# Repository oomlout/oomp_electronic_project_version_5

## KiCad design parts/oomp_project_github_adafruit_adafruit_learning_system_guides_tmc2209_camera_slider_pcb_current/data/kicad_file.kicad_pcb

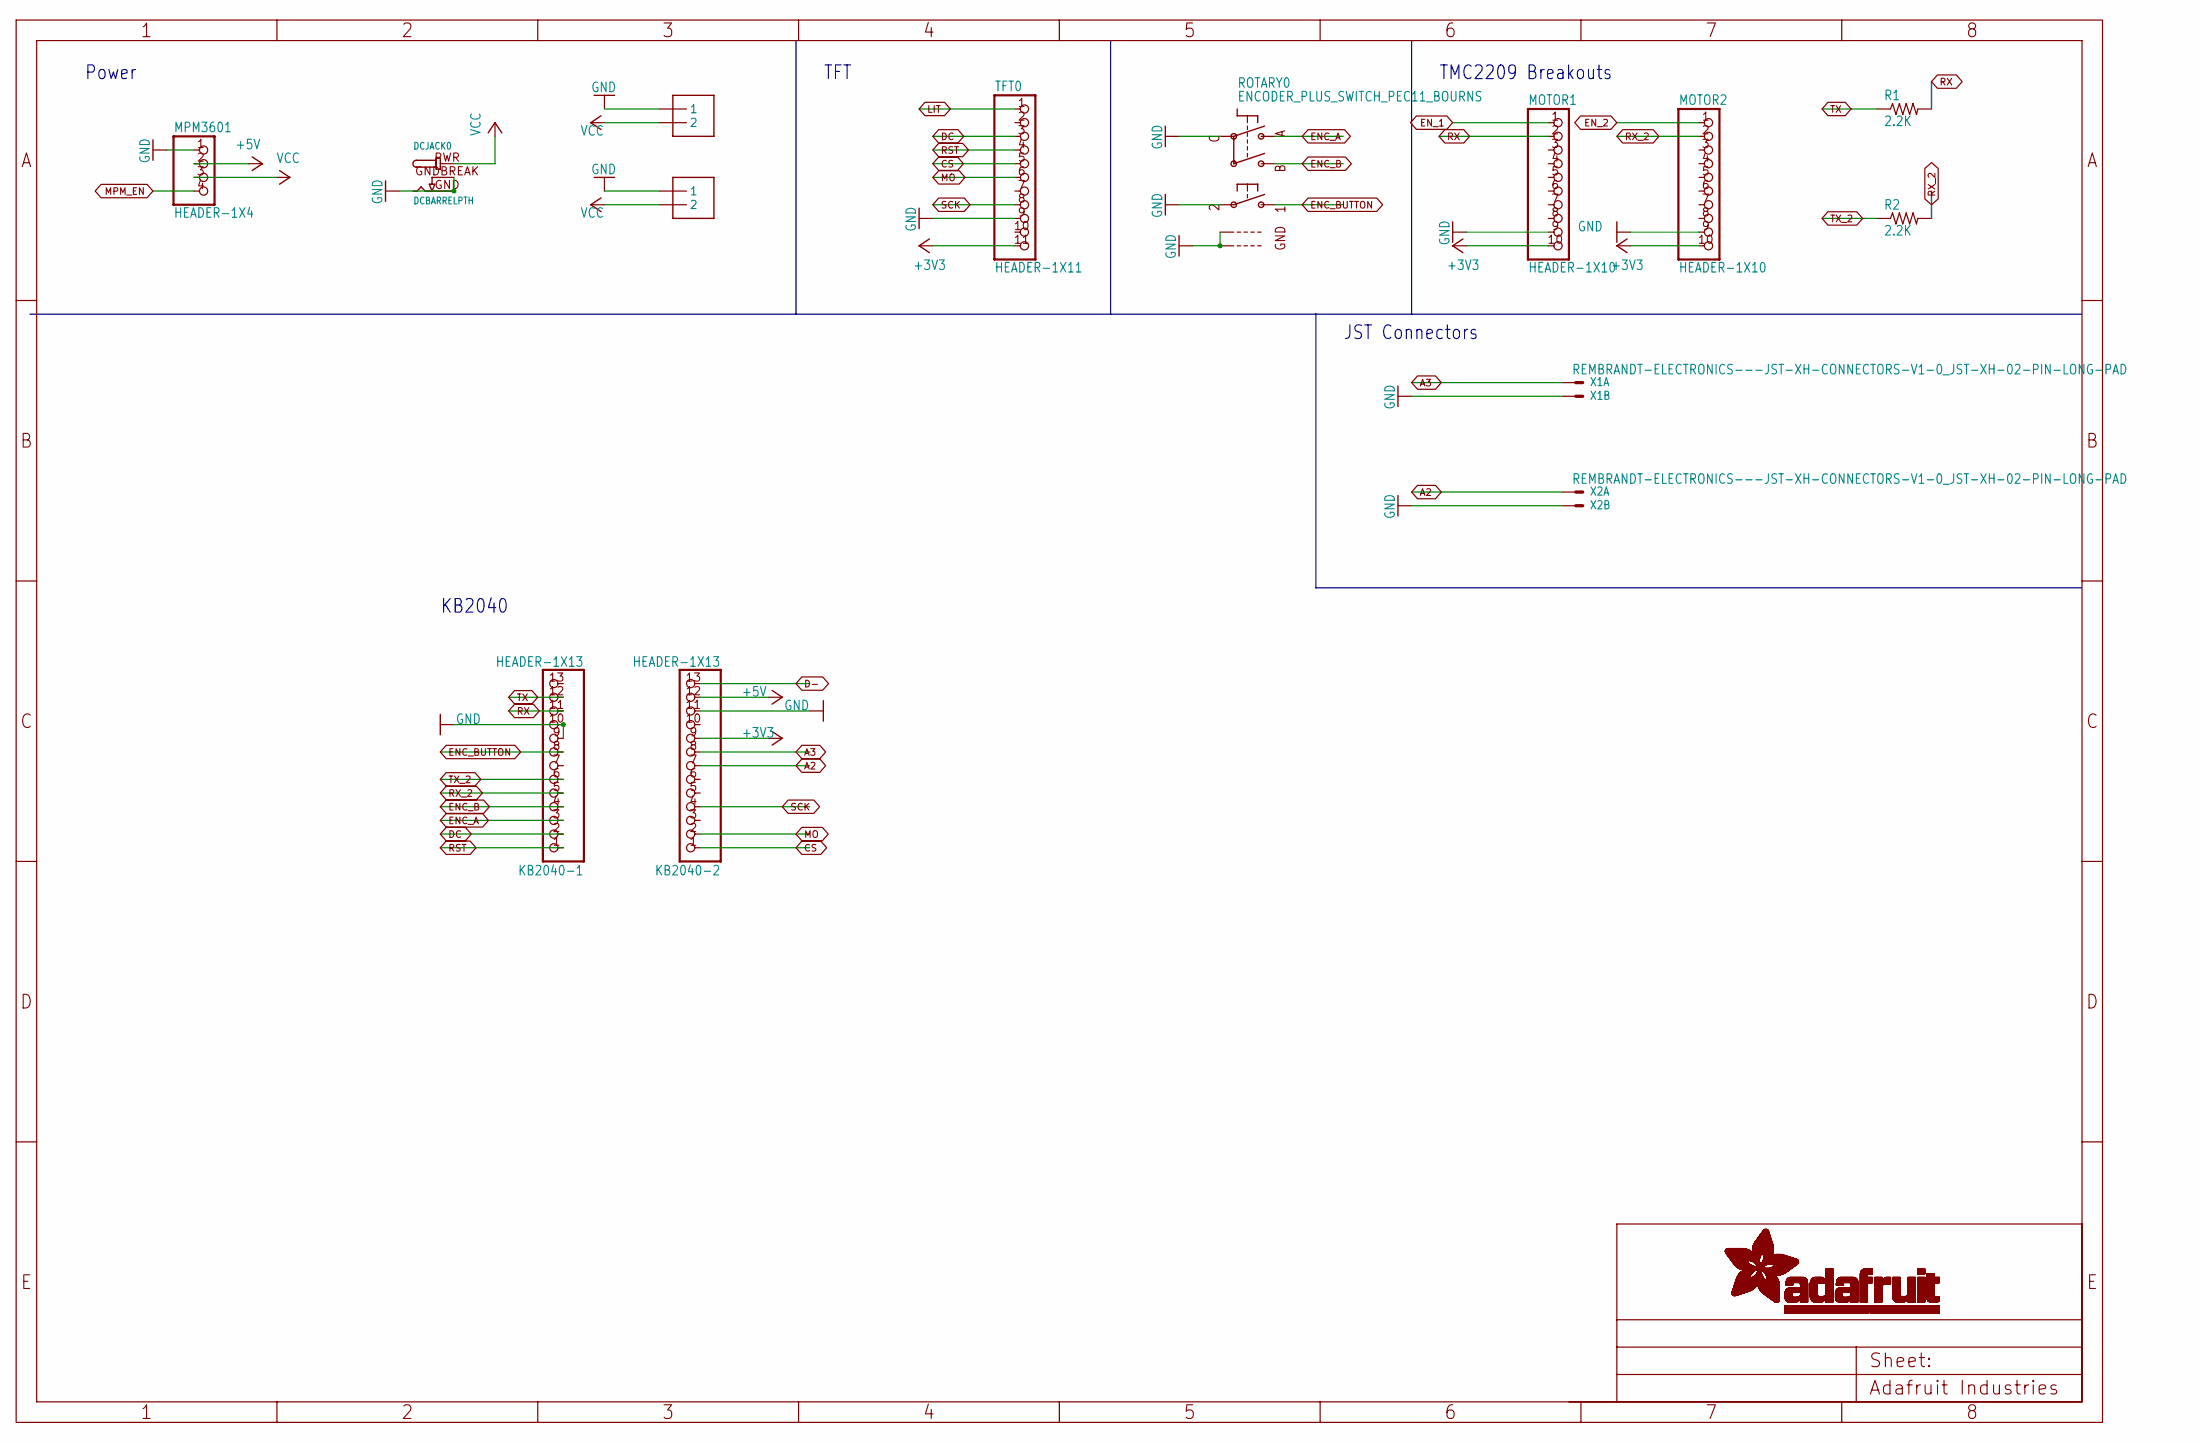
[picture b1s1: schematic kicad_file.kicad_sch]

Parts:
DCJACK0: DCBARRELPTH; DCJACK_2MM_PTH
J1, J2: 1X2-3.5MM
KB2040-1, KB2040-2: HEADER-1X13; 1X13_ROUND_70
MOTOR1, MOTOR2: HEADER-1X10; 1X10_OVAL
MPM3601: HEADER-1X4; 1X04_OVAL
R1, R2: 2.2K; 0309_12
ROTARY0: ENCODER_PLUS_SWITCH_PEC11_BOURNS; PEC11+SWITCH
TFT0: HEADER-1X11; 1X11_ROUND
X1, X2: REMBRANDT-ELECTRONICS---JST-XH-CONNECTORS-V1-0_JS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; REMBRANDT-ELECTRONICS---JST-XH-CONNECTORS-V1-0_JST-XH-02-PA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

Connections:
+3V3: KB2040-2.9, MOTOR1.10, MOTOR2.10, TFT0.11
+5V: KB2040-2.12, MPM3601.2
A2: KB2040-2.7, X2.1
A3: KB2040-2.8, X1.1
CS: KB2040-2.1, TFT0.5
D-: KB2040-2.13
DC: KB2040-1.2, TFT0.3
ENC_A: KB2040-1.3, ROTARY0.P$A
ENC_B: KB2040-1.4, ROTARY0.P$B
ENC_BUTTON: KB2040-1.8, ROTARY0.P$1
EN_1: MOTOR1.1
EN_2: MOTOR2.1
GND: DCJACK0.GND, DCJACK0.GNDBREAK, J1.1, J2.1, KB2040-1.9, KB2040-1.10, KB2040-2.11, MOTOR1.9, MOTOR2.9, MPM3601.1, ROTARY0.P$2, ROTARY0.P$C, ROTARY0.P$GND1, ROTARY0.P$GND2, TFT0.9, X1.2, X2.2
LIT: TFT0.1
MO: KB2040-2.2, TFT0.6
MPM_EN: MPM3601.4
RST: KB2040-1.1, TFT0.4
RX: KB2040-1.11, MOTOR1.2, R1.2
RX_2: KB2040-1.5, MOTOR2.2, R2.2
SCK: KB2040-2.4, TFT0.8
TX: KB2040-1.12, R1.1
TX_2: KB2040-1.6, R2.1
VCC: DCJACK0.PWR, J1.2, J2.2, MPM3601.3

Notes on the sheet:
TFT
JST Connectors
KB2040
TMC2209 Breakouts
Power

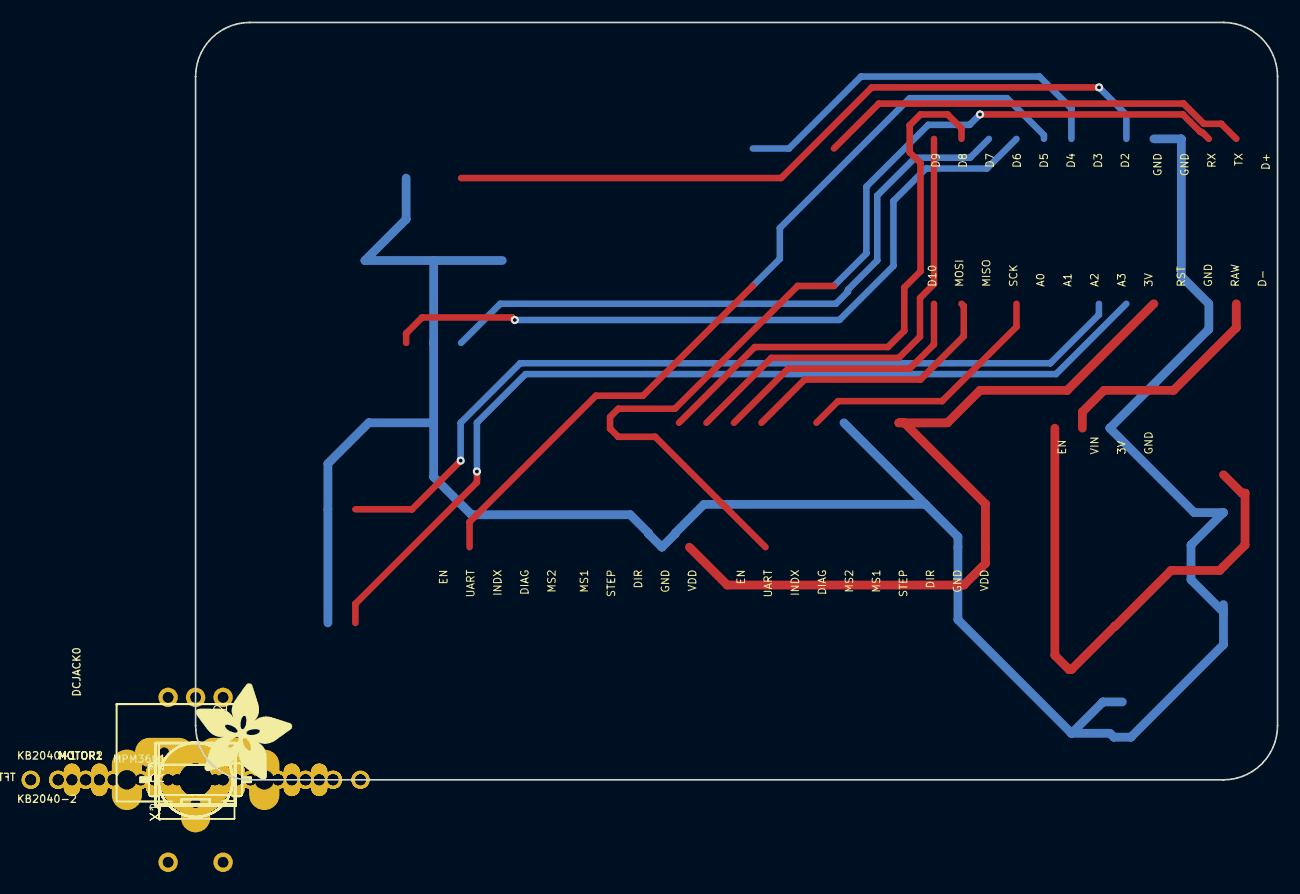
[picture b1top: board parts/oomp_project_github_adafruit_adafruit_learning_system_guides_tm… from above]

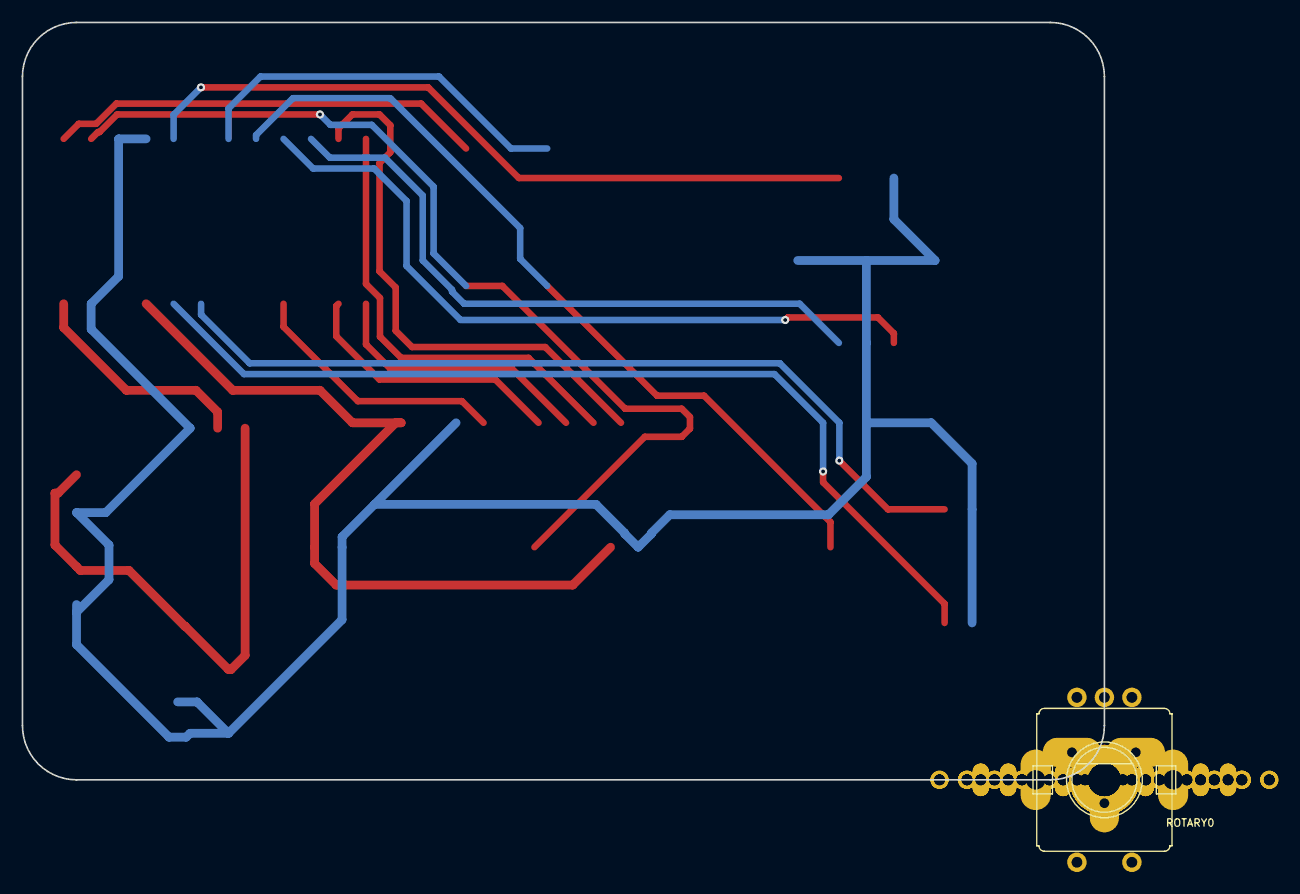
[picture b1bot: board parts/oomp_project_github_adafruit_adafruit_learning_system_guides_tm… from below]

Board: 2 copper layers, 100.0 x 70.0 mm, 114 parts (51 on the bottom side), 18 nets.

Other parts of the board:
E$1, E$2, E$3, E$5: MOUNTINGHOLE_3.0_PLATED
PLABEL0, PLABEL94: PLABEL0
PLABEL1, PLABEL6: PLABEL6
PLABEL2: PLABEL2
PLABEL3: PLABEL3
PLABEL4: PLABEL4
PLABEL5: PLABEL5
PLABEL7, PLABEL95: PLABEL1
PLABEL8: PLABEL8
PLABEL9: PLABEL9
PLABEL10: PLABEL10
PLABEL11: PLABEL11
PLABEL12: PLABEL12
PLABEL13: PLABEL13
PLABEL14: PLABEL14
PLABEL15: PLABEL15
PLABEL16, PLABEL96: PLABEL16
PLABEL17: PLABEL17
PLABEL18: PLABEL18
PLABEL19: PLABEL19
PLABEL21: PLABEL21
PLABEL24: PLABEL24
PLABEL25: PLABEL25
PLABEL26: PLABEL26
PLABEL27: PLABEL27
PLABEL28: PLABEL28
PLABEL29: PLABEL29
PLABEL30: PLABEL30
PLABEL31: PLABEL31
PLABEL32: PLABEL32
PLABEL33: PLABEL33
PLABEL34: PLABEL34
PLABEL35: PLABEL35
PLABEL36: PLABEL36
PLABEL41: PLABEL41
PLABEL42: PLABEL42
PLABEL43: PLABEL43
PLABEL44: PLABEL44
PLABEL45: PLABEL45
PLABEL46: PLABEL46
PLABEL47: PLABEL47
PLABEL48: PLABEL48
PLABEL49: PLABEL49
PLABEL50: PLABEL50
PLABEL51: PLABEL51
PLABEL52: PLABEL52
PLABEL53: PLABEL53
PLABEL54: PLABEL54
PLABEL55: PLABEL55
PLABEL56: PLABEL56
PLABEL57: PLABEL57
PLABEL58: PLABEL58
PLABEL59: PLABEL59
PLABEL60: PLABEL60
PLABEL61: PLABEL61
PLABEL62: PLABEL62
PLABEL63: PLABEL63
PLABEL64: PLABEL64
PLABEL65: PLABEL65
PLABEL66: PLABEL66
PLABEL67: PLABEL67
PLABEL68: PLABEL68
PLABEL69: PLABEL69
PLABEL70: PLABEL70
PLABEL71: PLABEL71
PLABEL72: PLABEL72
PLABEL73: PLABEL73
PLABEL74: PLABEL74
PLABEL75: PLABEL75
PLABEL76: PLABEL76
PLABEL77: PLABEL77
PLABEL78: PLABEL78
PLABEL79: PLABEL79
PLABEL80: PLABEL80
PLABEL81: PLABEL81
PLABEL82: PLABEL82
PLABEL83: PLABEL83
PLABEL84: PLABEL84
PLABEL85: PLABEL85
PLABEL86: PLABEL86
PLABEL87: PLABEL87
PLABEL88: PLABEL88
PLABEL89: PLABEL89
PLABEL90: PLABEL90
PLABEL91: PLABEL91
PLABEL92: PLABEL92
PLABEL93: PLABEL93
PLABEL200: PLABEL200
PLABEL201: PLABEL201
PLABEL202: PLABEL202
PLABEL203: PLABEL203
PLABEL204: PLABEL204
U$1: ADAFRUIT_9MM

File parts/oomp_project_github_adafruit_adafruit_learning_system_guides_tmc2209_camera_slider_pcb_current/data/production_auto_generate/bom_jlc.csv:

Comment,Designator,Footprint,LCSC Part #
,MPM3601,TMC2209_Camera_Slider_PCB_revB-import-fps:1X04_OVAL,C42431795
,"MOTOR1,MOTOR2",TMC2209_Camera_Slider_PCB_revB-import-fps:1X10_OVAL,C57369
,TFT0,TMC2209_Camera_Slider_PCB_revB-import-fps:1X11_ROUND,C2894934
,"KB2040-1,KB2040-2",TMC2209_Camera_Slider_PCB_revB-import-fps:1X13_ROUND_70,C2894936
,U$1,TMC2209_Camera_Slider_PCB_revB-import-fps:ADAFRUIT_9MM,
,DCJACK0,TMC2209_Camera_Slider_PCB_revB-import-fps:DCJACK_2MM_PTH,
,"PLABEL0,PLABEL94",TMC2209_Camera_Slider_PCB_revB-import-fps:PLABEL0,
,"PLABEL7,PLABEL95",TMC2209_Camera_Slider_PCB_revB-import-fps:PLABEL1,
,PLABEL10,TMC2209_Camera_Slider_PCB_revB-import-fps:PLABEL10,
,PLABEL11,TMC2209_Camera_Slider_PCB_revB-import-fps:PLABEL11,
,PLABEL12,TMC2209_Camera_Slider_PCB_revB-import-fps:PLABEL12,
,PLABEL13,TMC2209_Camera_Slider_PCB_revB-import-fps:PLABEL13,
,PLABEL14,TMC2209_Camera_Slider_PCB_revB-import-fps:PLABEL14,
,PLABEL15,TMC2209_Camera_Slider_PCB_revB-import-fps:PLABEL15,
,"PLABEL16,PLABEL96",TMC2209_Camera_Slider_PCB_revB-import-fps:PLABEL16,
,PLABEL17,TMC2209_Camera_Slider_PCB_revB-import-fps:PLABEL17,
,PLABEL18,TMC2209_Camera_Slider_PCB_revB-import-fps:PLABEL18,
,PLABEL19,TMC2209_Camera_Slider_PCB_revB-import-fps:PLABEL19,
,PLABEL2,TMC2209_Camera_Slider_PCB_revB-import-fps:PLABEL2,
,PLABEL200,TMC2209_Camera_Slider_PCB_revB-import-fps:PLABEL200,
,PLABEL201,TMC2209_Camera_Slider_PCB_revB-import-fps:PLABEL201,
,PLABEL202,TMC2209_Camera_Slider_PCB_revB-import-fps:PLABEL202,
,PLABEL203,TMC2209_Camera_Slider_PCB_revB-import-fps:PLABEL203,
,PLABEL204,TMC2209_Camera_Slider_PCB_revB-import-fps:PLABEL204,
,PLABEL21,TMC2209_Camera_Slider_PCB_revB-import-fps:PLABEL21,
,PLABEL24,TMC2209_Camera_Slider_PCB_revB-import-fps:PLABEL24,
,PLABEL25,TMC2209_Camera_Slider_PCB_revB-import-fps:PLABEL25,
,PLABEL26,TMC2209_Camera_Slider_PCB_revB-import-fps:PLABEL26,
,PLABEL27,TMC2209_Camera_Slider_PCB_revB-import-fps:PLABEL27,
,PLABEL28,TMC2209_Camera_Slider_PCB_revB-import-fps:PLABEL28,
,PLABEL29,TMC2209_Camera_Slider_PCB_revB-import-fps:PLABEL29,
,PLABEL3,TMC2209_Camera_Slider_PCB_revB-import-fps:PLABEL3,
,PLABEL30,TMC2209_Camera_Slider_PCB_revB-import-fps:PLABEL30,
,PLABEL31,TMC2209_Camera_Slider_PCB_revB-import-fps:PLABEL31,
,PLABEL32,TMC2209_Camera_Slider_PCB_revB-import-fps:PLABEL32,
,PLABEL33,TMC2209_Camera_Slider_PCB_revB-import-fps:PLABEL33,
,PLABEL34,TMC2209_Camera_Slider_PCB_revB-import-fps:PLABEL34,
,PLABEL35,TMC2209_Camera_Slider_PCB_revB-import-fps:PLABEL35,
,PLABEL36,TMC2209_Camera_Slider_PCB_revB-import-fps:PLABEL36,
,PLABEL4,TMC2209_Camera_Slider_PCB_revB-import-fps:PLABEL4,
,PLABEL41,TMC2209_Camera_Slider_PCB_revB-import-fps:PLABEL41,
,PLABEL42,TMC2209_Camera_Slider_PCB_revB-import-fps:PLABEL42,
,PLABEL43,TMC2209_Camera_Slider_PCB_revB-import-fps:PLABEL43,
,PLABEL44,TMC2209_Camera_Slider_PCB_revB-import-fps:PLABEL44,
,PLABEL45,TMC2209_Camera_Slider_PCB_revB-import-fps:PLABEL45,
,PLABEL46,TMC2209_Camera_Slider_PCB_revB-import-fps:PLABEL46,
,PLABEL47,TMC2209_Camera_Slider_PCB_revB-import-fps:PLABEL47,
,PLABEL48,TMC2209_Camera_Slider_PCB_revB-import-fps:PLABEL48,
,PLABEL49,TMC2209_Camera_Slider_PCB_revB-import-fps:PLABEL49,
,PLABEL5,TMC2209_Camera_Slider_PCB_revB-import-fps:PLABEL5,
,PLABEL50,TMC2209_Camera_Slider_PCB_revB-import-fps:PLABEL50,
,PLABEL51,TMC2209_Camera_Slider_PCB_revB-import-fps:PLABEL51,
,PLABEL52,TMC2209_Camera_Slider_PCB_revB-import-fps:PLABEL52,
,PLABEL53,TMC2209_Camera_Slider_PCB_revB-import-fps:PLABEL53,
,PLABEL54,TMC2209_Camera_Slider_PCB_revB-import-fps:PLABEL54,
,PLABEL55,TMC2209_Camera_Slider_PCB_revB-import-fps:PLABEL55,
,PLABEL56,TMC2209_Camera_Slider_PCB_revB-import-fps:PLABEL56,
,PLABEL57,TMC2209_Camera_Slider_PCB_revB-import-fps:PLABEL57,
,PLABEL58,TMC2209_Camera_Slider_PCB_revB-import-fps:PLABEL58,
,PLABEL59,TMC2209_Camera_Slider_PCB_revB-import-fps:PLABEL59,
,"PLABEL1,PLABEL6",TMC2209_Camera_Slider_PCB_revB-import-fps:PLABEL6,
,PLABEL60,TMC2209_Camera_Slider_PCB_revB-import-fps:PLABEL60,
,PLABEL61,TMC2209_Camera_Slider_PCB_revB-import-fps:PLABEL61,
,PLABEL62,TMC2209_Camera_Slider_PCB_revB-import-fps:PLABEL62,
,PLABEL63,TMC2209_Camera_Slider_PCB_revB-import-fps:PLABEL63,
,PLABEL64,TMC2209_Camera_Slider_PCB_revB-import-fps:PLABEL64,
,PLABEL65,TMC2209_Camera_Slider_PCB_revB-import-fps:PLABEL65,
,PLABEL66,TMC2209_Camera_Slider_PCB_revB-import-fps:PLABEL66,
,PLABEL67,TMC2209_Camera_Slider_PCB_revB-import-fps:PLABEL67,
,PLABEL68,TMC2209_Camera_Slider_PCB_revB-import-fps:PLABEL68,
,PLABEL69,TMC2209_Camera_Slider_PCB_revB-import-fps:PLABEL69,
,PLABEL70,TMC2209_Camera_Slider_PCB_revB-import-fps:PLABEL70,
,PLABEL71,TMC2209_Camera_Slider_PCB_revB-import-fps:PLABEL71,
,PLABEL72,TMC2209_Camera_Slider_PCB_revB-import-fps:PLABEL72,
,PLABEL73,TMC2209_Camera_Slider_PCB_revB-import-fps:PLABEL73,
,PLABEL74,TMC2209_Camera_Slider_PCB_revB-import-fps:PLABEL74,
,PLABEL75,TMC2209_Camera_Slider_PCB_revB-import-fps:PLABEL75,
,PLABEL76,TMC2209_Camera_Slider_PCB_revB-import-fps:PLABEL76,
,PLABEL77,TMC2209_Camera_Slider_PCB_revB-import-fps:PLABEL77,
,PLABEL78,TMC2209_Camera_Slider_PCB_revB-import-fps:PLABEL78,
,PLABEL79,TMC2209_Camera_Slider_PCB_revB-import-fps:PLABEL79,
,PLABEL8,TMC2209_Camera_Slider_PCB_revB-import-fps:PLABEL8,
,PLABEL80,TMC2209_Camera_Slider_PCB_revB-import-fps:PLABEL80,
,PLABEL81,TMC2209_Camera_Slider_PCB_revB-import-fps:PLABEL81,
,PLABEL82,TMC2209_Camera_Slider_PCB_revB-import-fps:PLABEL82,
,PLABEL83,TMC2209_Camera_Slider_PCB_revB-import-fps:PLABEL83,
,PLABEL84,TMC2209_Camera_Slider_PCB_revB-import-fps:PLABEL84,
,PLABEL85,TMC2209_Camera_Slider_PCB_revB-import-fps:PLABEL85,
,PLABEL86,TMC2209_Camera_Slider_PCB_revB-import-fps:PLABEL86,
,PLABEL87,TMC2209_Camera_Slider_PCB_revB-import-fps:PLABEL87,
,PLABEL88,TMC2209_Camera_Slider_PCB_revB-import-fps:PLABEL88,
,PLABEL89,TMC2209_Camera_Slider_PCB_revB-import-fps:PLABEL89,
,PLABEL9,TMC2209_Camera_Slider_PCB_revB-import-fps:PLABEL9,
,PLABEL90,TMC2209_Camera_Slider_PCB_revB-import-fps:PLABEL90,
,PLABEL91,TMC2209_Camera_Slider_PCB_revB-import-fps:PLABEL91,
,PLABEL92,TMC2209_Camera_Slider_PCB_revB-import-fps:PLABEL92,
,PLABEL93,TMC2209_Camera_Slider_PCB_revB-import-fps:PLABEL93,
1X2-3.5MM,"J1,J2",TMC2209_Camera_Slider_PCB_revB-import-fps:1X2-3.5MM,C492401
2.2K,"R1,R2",TMC2209_Camera_Slider_PCB_revB-import-fps:0309_12,
REMBRANDT-ELECTRONICS---JST-XH-CONNECTORS-V1-0_JST-XH-02-PIN-LONG-PAD,"X1,X2",TMC2209_Camera_Slider_PCB_revB-import-fps:REMBRANDT-ELECTRONICS---JST-XH-CONNECTORS-V1-0_JST-XH-02-PACKAGE-LONG-PAD,

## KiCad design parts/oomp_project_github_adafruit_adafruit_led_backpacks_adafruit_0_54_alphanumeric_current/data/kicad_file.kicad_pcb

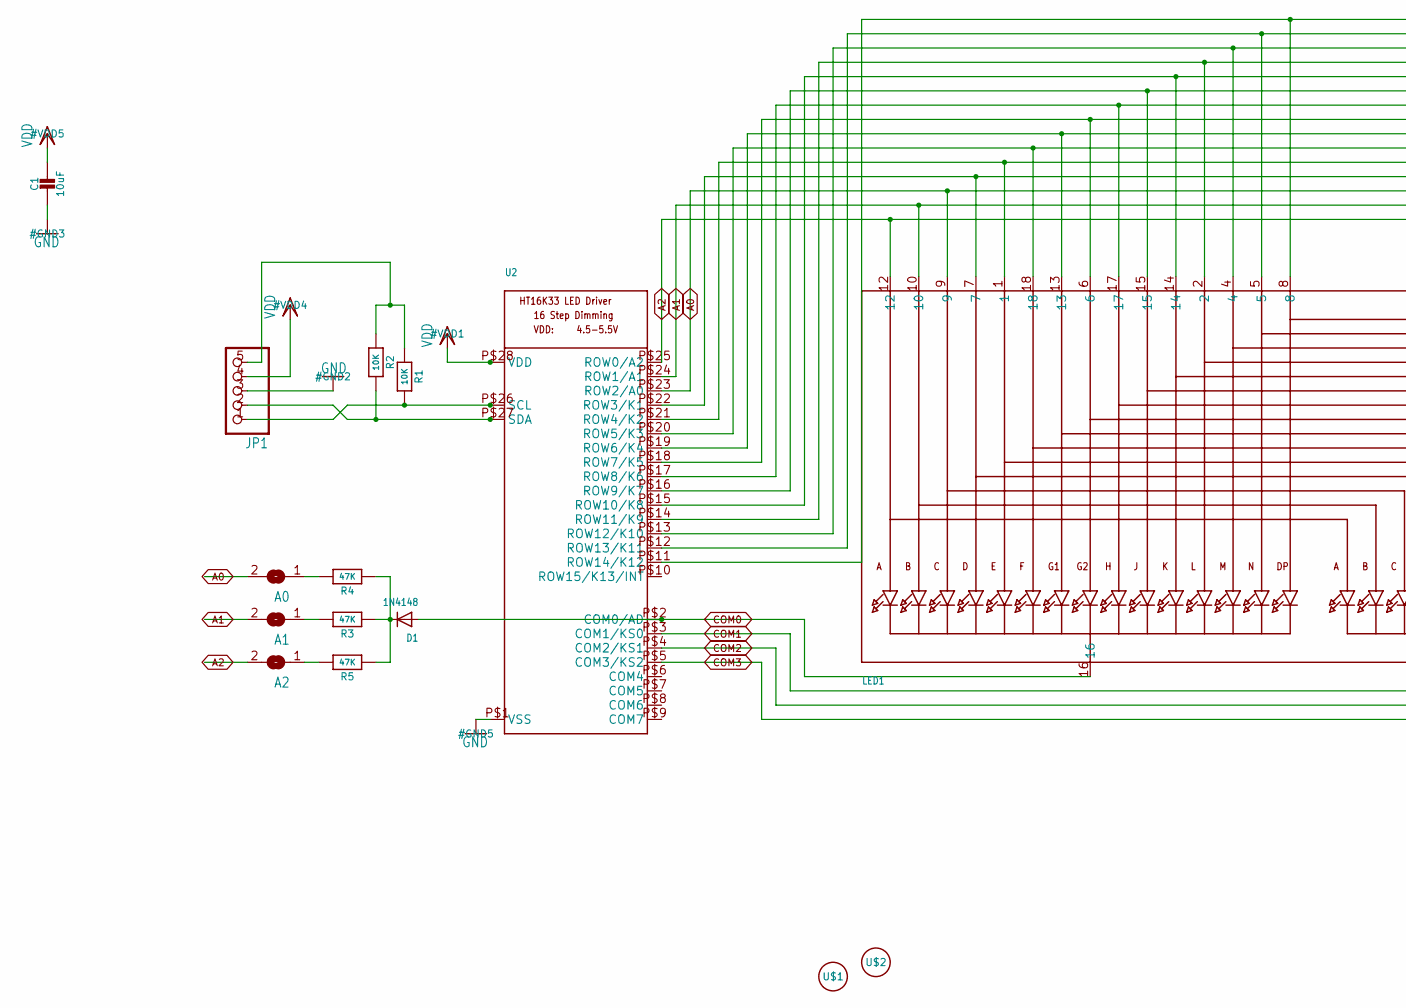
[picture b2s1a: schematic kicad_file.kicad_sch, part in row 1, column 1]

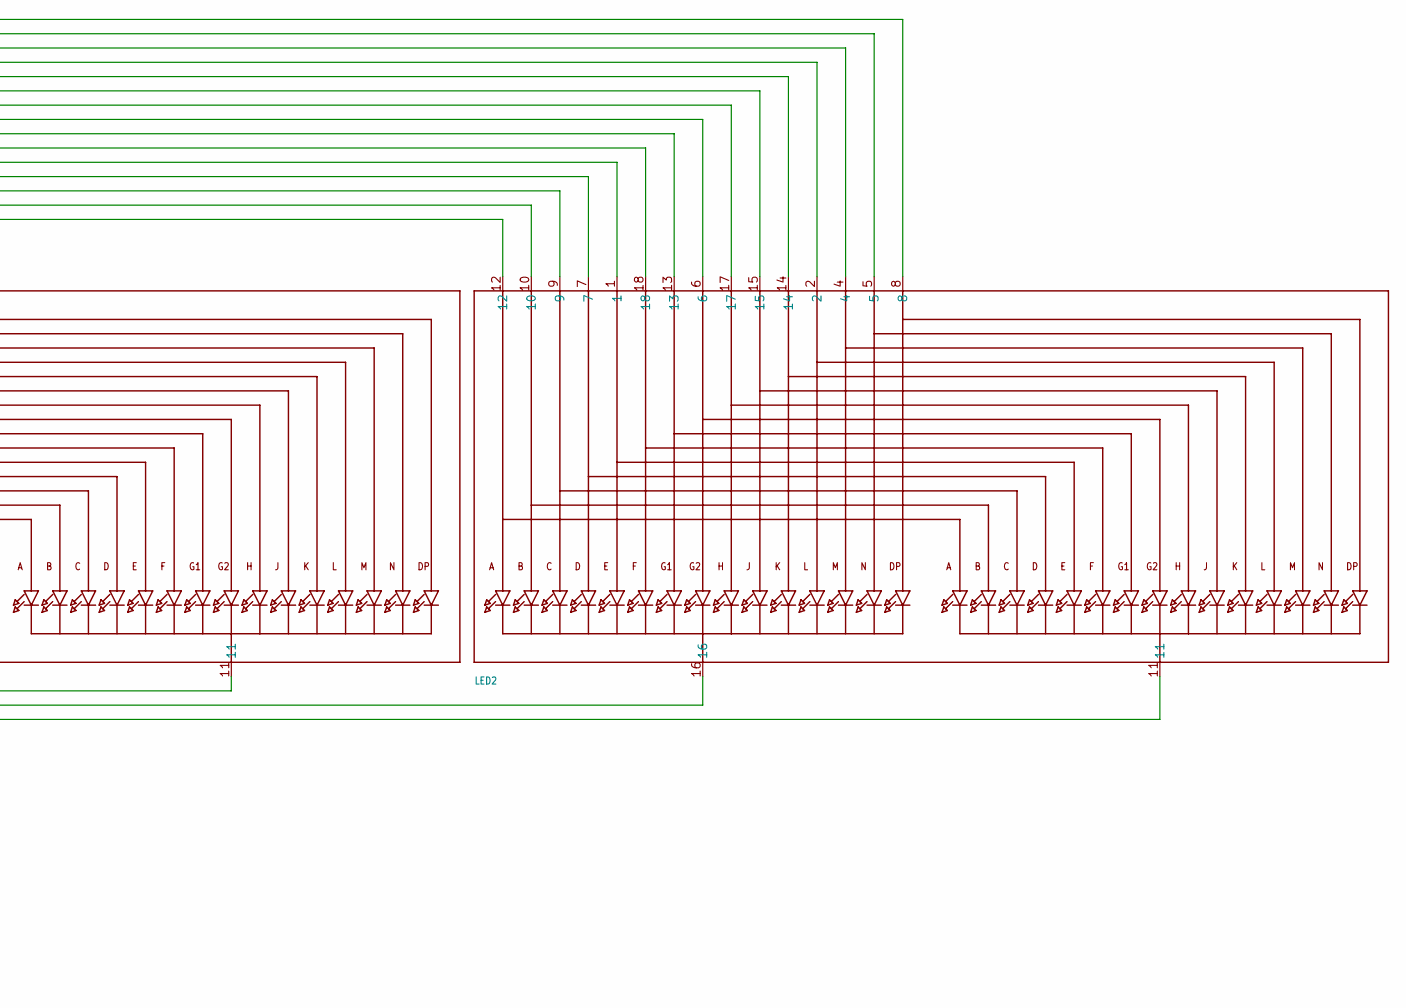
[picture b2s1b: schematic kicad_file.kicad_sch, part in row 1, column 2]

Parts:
A0, A1, A2: SOLDERJUMPERREFLOW_NOPASTE; SOLDERJUMPER_REFLOW_NOPASTE
C1: 10uF; 0805-NO
D1: 1N4148; SOD-323F
JP1: HEADER-1X570MIL; 1X05_ROUND_70
LED1, LED2: DISP_SEGMENT_STARBURST_DUAL_COMMONCATHODE; SEGMENT_STARTBUST_DUAL_KWA-541CBB
R1, R2: 10K; 0805-NO
R3, R4, R5: 47K; 0805-NO
U2: HT16K33_SOP28; SOP28_300MIL
U$1, U$2: FIDUCIAL; FIDUCIAL_1MM

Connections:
A0: A0.2, LED1.9, LED2.9, U2.P$23 (ROW2/A0)
A1: A1.2, LED1.10, LED2.10, U2.P$24 (ROW1/A1)
A2: A2.2, LED1.12, LED2.12, U2.P$25 (ROW0/A2)
COM0: D1.A, LED1.16, U2.P$2 (COM0/AD)
COM1: LED1.11, U2.P$3 (COM1/KS0)
COM2: LED2.16, U2.P$4 (COM2/KS1)
COM3: LED2.11, U2.P$5 (COM3/KS2)
GND: C1.2, JP1.3, U2.P$1 (VSS)
unnamed: D1.C, R3.1, R4.1, R5.1
unnamed: JP1.5, R1.1, R2.1
unnamed: LED1.17, LED2.17, U2.P$17 (ROW8/K6)
unnamed: LED1.15, LED2.15, U2.P$16 (ROW9/K7)
unnamed: LED1.14, LED2.14, U2.P$15 (ROW10/K8)
unnamed: A2.1, R5.2
unnamed: LED1.2, LED2.2, U2.P$14 (ROW11/K9)
unnamed: LED1.4, LED2.4, U2.P$13 (ROW12/K10)
unnamed: LED1.7, LED2.7, U2.P$22 (ROW3/K1)
unnamed: LED1.1, LED2.1, U2.P$21 (ROW4/K2)
unnamed: LED1.18, LED2.18, U2.P$20 (ROW5/K3)
unnamed: LED1.13, LED2.13, U2.P$19 (ROW6/K4)
unnamed: LED1.5, LED2.5, U2.P$12 (ROW13/K11)
unnamed: LED1.8, LED2.8, U2.P$11 (ROW14/K12)
unnamed: LED1.6, LED2.6, U2.P$18 (ROW7/K5)
unnamed: A1.1, R3.2
unnamed: A0.1, R4.2
SCL: JP1.1, R1.2, U2.P$26 (SCL)
SDA: JP1.2, R2.2, U2.P$27 (SDA)
VDD: C1.1, JP1.4, U2.P$28 (VDD)

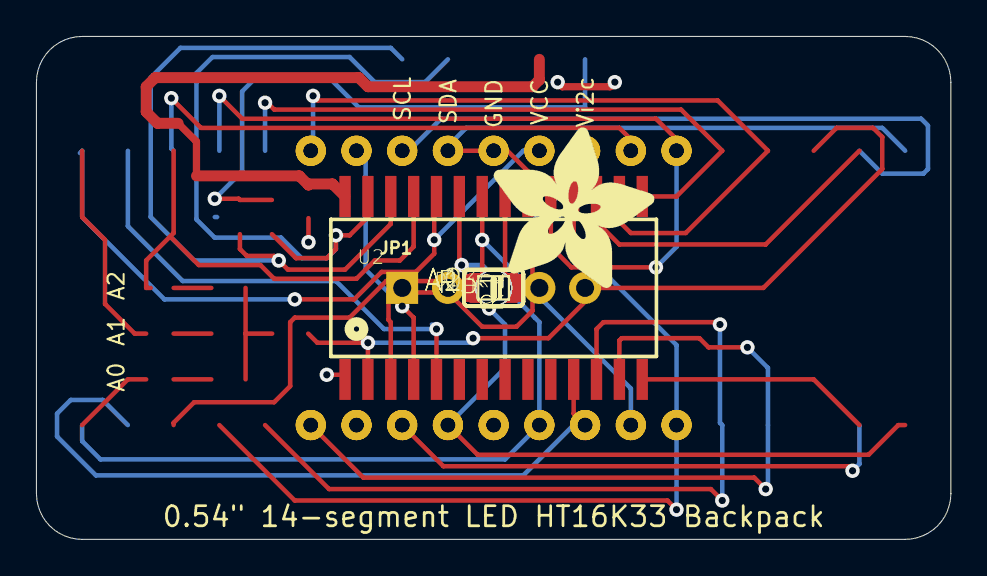
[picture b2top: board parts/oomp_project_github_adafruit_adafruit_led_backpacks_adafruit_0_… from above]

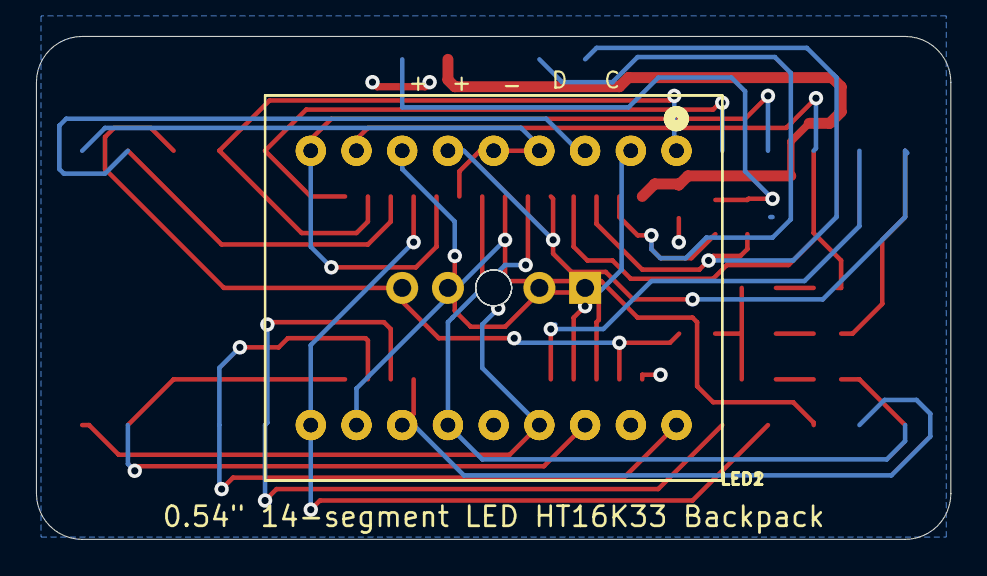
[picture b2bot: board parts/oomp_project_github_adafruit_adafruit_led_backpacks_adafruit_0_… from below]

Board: 16 copper layers, 50.8 x 27.9 mm, 21 parts (2 on the bottom side), 28 nets.

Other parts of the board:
U$3: ADAFRUIT_9MM
UNK_HOLE_0: dummyfp0
UNK_HOLE_1: dummyfp1
UNK_HOLE_2: dummyfp2
UNK_HOLE_3: dummyfp3

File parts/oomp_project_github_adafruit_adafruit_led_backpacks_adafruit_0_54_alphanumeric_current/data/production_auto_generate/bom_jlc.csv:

Comment,Designator,Footprint,LCSC Part #
,JP1,Adafruit 0.54 Alphanumeric v0.1-import-fps:1X05_ROUND_70,C42431835
,U$3,Adafruit 0.54 Alphanumeric v0.1-import-fps:ADAFRUIT_9MM,
,"LED1,LED2",Adafruit 0.54 Alphanumeric v0.1-import-fps:SEGMENT_STARTBUST_DUAL_KWA-541CBB,
,"A0,A1,A2",Adafruit 0.54 Alphanumeric v0.1-import-fps:SOLDERJUMPER_REFLOW_NOPASTE,
,U2,Adafruit 0.54 Alphanumeric v0.1-import-fps:SOP28_300MIL,
10K,"R1,R2",Adafruit 0.54 Alphanumeric v0.1-import-fps:0805-NO,C17414
10uF,C1,Adafruit 0.54 Alphanumeric v0.1-import-fps:0805-NO,
1N4148,D1,Adafruit 0.54 Alphanumeric v0.1-import-fps:SOD-323F,
47K,"R3,R4,R5",Adafruit 0.54 Alphanumeric v0.1-import-fps:0805-NO,C17713
FIDUCIAL,"U$1,U$2",Adafruit 0.54 Alphanumeric v0.1-import-fps:FIDUCIAL_1MM,

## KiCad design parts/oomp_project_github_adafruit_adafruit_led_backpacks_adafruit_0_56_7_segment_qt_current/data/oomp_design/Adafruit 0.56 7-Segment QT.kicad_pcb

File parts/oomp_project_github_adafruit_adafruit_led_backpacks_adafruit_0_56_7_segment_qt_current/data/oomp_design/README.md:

# OOMP KiCad design copy

Open `Adafruit 0.56 7-Segment QT.kicad_pro` (or the `.kicad_pcb` / `.kicad_sch`) in KiCad. Local OOMP libraries are under `libraries/`. Original inputs are preserved in [../original/](../original/).

Only verified unchanged installed KiCad defaults were renamed. Modified, custom, unmatched and unavailable items remain unchanged. Soldering variants are never swapped during conversion. Existing pad coordinates, nets and UUIDs are preserved.

See [conversion_report.yaml](conversion_report.yaml) for every conversion and skip. Copy this directory before editing; regeneration refuses to overwrite edited design files.

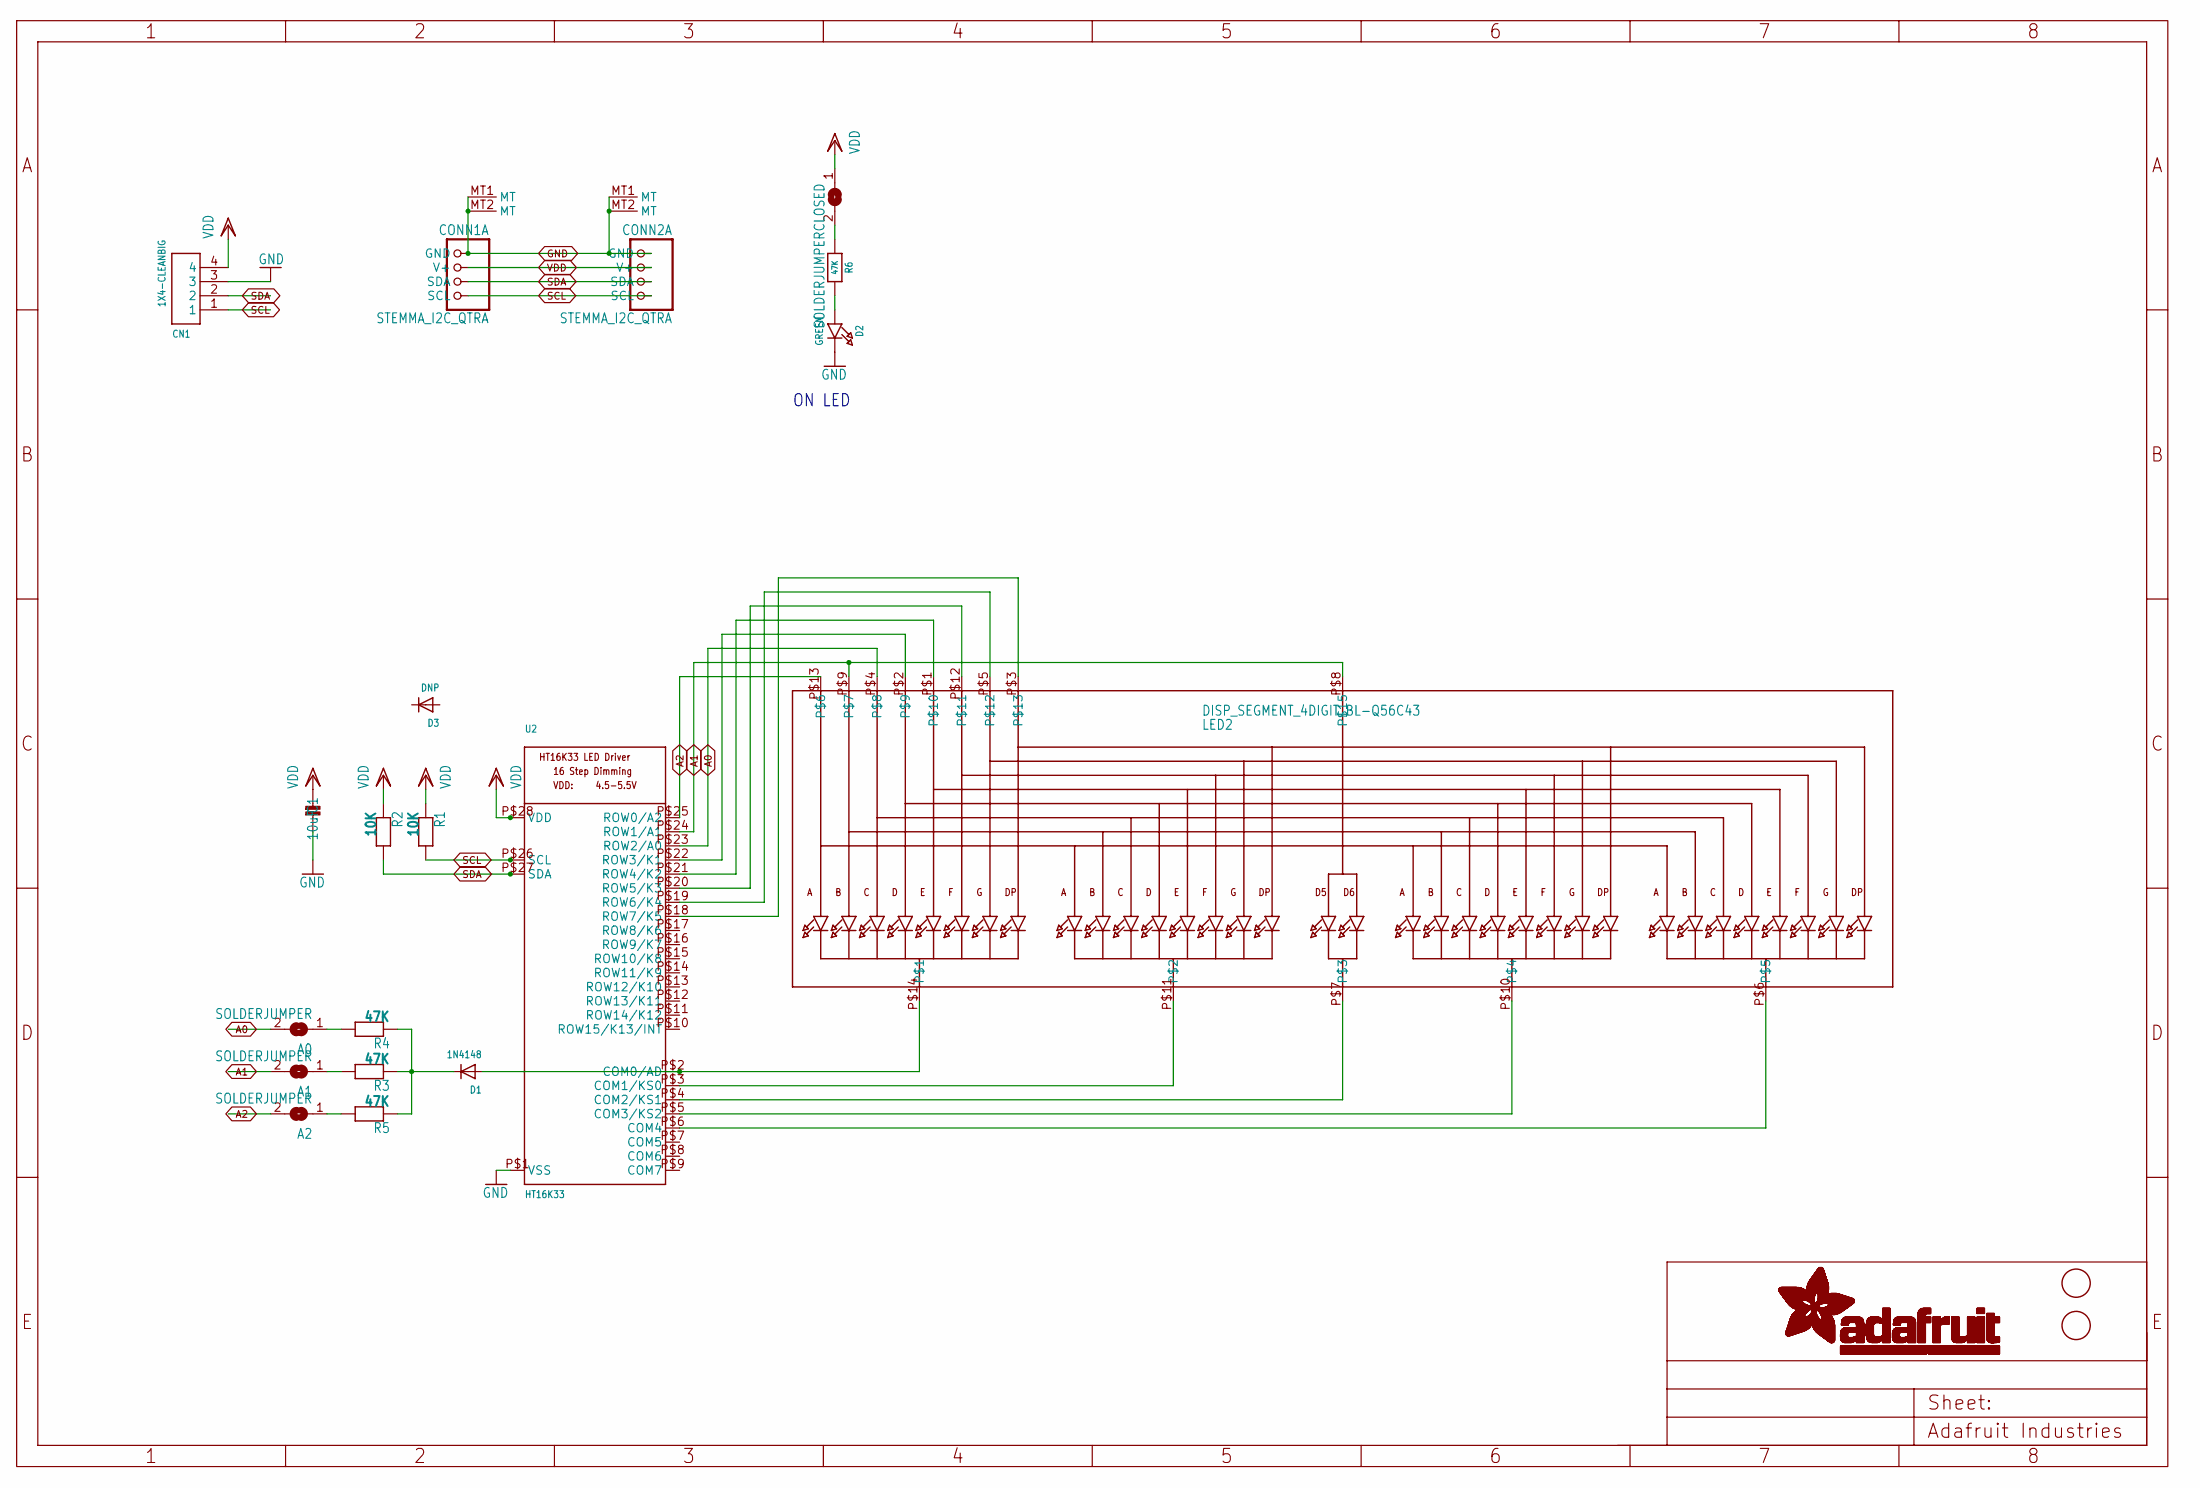
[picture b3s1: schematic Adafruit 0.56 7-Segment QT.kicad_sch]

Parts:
A0, A1, A2: SOLDERJUMPER; SOLDERJUMPER_ARROW_NOPASTE
C1: 10uF; 0805_10MGAP
CN1: 1X4-CLEANBIG; 1X04-CLEANBIG
CONN1, CONN2: STEMMA_I2C_QTRA; JST_SH4_RA
D1: 1N4148; SOD-323F
D2: GREEN; CHIPLED_0603_NOOUTLINE
D3: DNP; SOD-323F
LED2: DISP_SEGMENT_4DIGIT_BL-Q56C43; SEGMENT-BL-Q56C43
LEDJMP0: SOLDERJUMPERCLOSED; SOLDERJUMPER_CLOSEDWIRE
R1, R2: 10K; 0603-NO
R3, R4, R5, R6: 47K; 0603-NO
U2: HT16K33; SOP28_300MIL_SKINNY
U$1, U$2: FIDUCIAL; FIDUCIAL_1MM

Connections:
A0: A0.2, LED2.P$4, U2.P$23 (ROW2/A0)
A1: A1.2, LED2.P$8, LED2.P$9, U2.P$24 (ROW1/A1)
A2: A2.2, LED2.P$13, U2.P$25 (ROW0/A2)
GND: C1.2, CN1.3, CONN1.1 (GND), CONN1.MT1 (MT), CONN1.MT2 (MT), CONN2.1 (GND), CONN2.MT1 (MT), CONN2.MT2 (MT), D2.C, U2.P$1 (VSS)
unnamed: D1.C, R3.1, R4.1, R5.1
unnamed: D1.A, LED2.P$14, U2.P$2 (COM0/AD)
unnamed: LED2.P$11, U2.P$3 (COM1/KS0)
unnamed: LED2.P$7, U2.P$4 (COM2/KS1)
unnamed: LED2.P$10, U2.P$5 (COM3/KS2)
unnamed: LED2.P$6, U2.P$6 (COM4)
unnamed: A2.1, R5.2
unnamed: D2.A, R6.2
unnamed: LEDJMP0.2, R6.1
unnamed: LED2.P$2, U2.P$22 (ROW3/K1)
unnamed: LED2.P$1, U2.P$21 (ROW4/K2)
unnamed: LED2.P$12, U2.P$20 (ROW5/K3)
unnamed: LED2.P$5, U2.P$19 (ROW6/K4)
unnamed: LED2.P$3, U2.P$18 (ROW7/K5)
unnamed: A1.1, R3.2
unnamed: A0.1, R4.2
SCL: CN1.1, CONN1.4 (SCL), CONN2.4 (SCL), R1.2, U2.P$26 (SCL)
SDA: CN1.2, CONN1.3 (SDA), CONN2.3 (SDA), R2.2, U2.P$27 (SDA)
VDD: C1.1, CN1.4, CONN1.2 (V+), CONN2.2 (V+), LEDJMP0.1, R1.1, R2.1, U2.P$28 (VDD)

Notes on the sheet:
ON LED

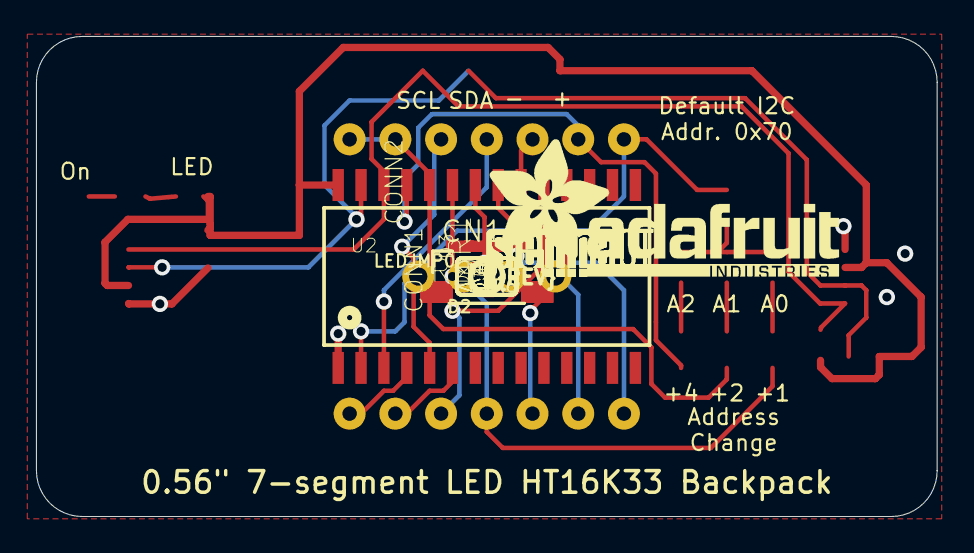
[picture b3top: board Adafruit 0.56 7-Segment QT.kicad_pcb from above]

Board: 16 copper layers, 50.0 x 26.7 mm, 29 parts (1 on the bottom side), 23 nets.

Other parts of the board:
U$3: ADAFRUIT_TEXT_20MM
U$5, U$6: STEMMAQT
U$7: PCBFEAT-REV-040
UNK_HOLE_0: dummyfp0
UNK_HOLE_1: dummyfp1
UNK_HOLE_2: dummyfp2
UNK_HOLE_3: dummyfp3

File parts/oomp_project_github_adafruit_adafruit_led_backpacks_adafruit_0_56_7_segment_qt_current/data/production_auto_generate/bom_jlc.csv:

Comment,Designator,Footprint,LCSC Part #
,U$3,Adafruit 0.56 7-Segment QT-import-fps:ADAFRUIT_TEXT_20MM,
,U$7,Adafruit 0.56 7-Segment QT-import-fps:PCBFEAT-REV-040,
,"A0,A1,A2",Adafruit 0.56 7-Segment QT-import-fps:SOLDERJUMPER_ARROW_NOPASTE,
,LEDJMP0,Adafruit 0.56 7-Segment QT-import-fps:SOLDERJUMPER_CLOSEDWIRE,
,"U$5,U$6",Adafruit 0.56 7-Segment QT-import-fps:STEMMAQT,
10K,"R1,R2",Adafruit 0.56 7-Segment QT-import-fps:0603-NO,C98220
10uF,C1,Adafruit 0.56 7-Segment QT-import-fps:0805_10MGAP,
1N4148,D1,Adafruit 0.56 7-Segment QT-import-fps:SOD-323F,
1X4-CLEANBIG,CN1,Adafruit 0.56 7-Segment QT-import-fps:1X04-CLEANBIG,
47K,"R3,R4,R5,R6",Adafruit 0.56 7-Segment QT-import-fps:0603-NO,C2907042
DNP,D3,Adafruit 0.56 7-Segment QT-import-fps:SOD-323F,
FIDUCIAL,"U$1,U$2",Adafruit 0.56 7-Segment QT-import-fps:FIDUCIAL_1MM,
GREEN,D2,Adafruit 0.56 7-Segment QT-import-fps:CHIPLED_0603_NOOUTLINE,
HT16K33,U2,Adafruit 0.56 7-Segment QT-import-fps:SOP28_300MIL_SKINNY,
STEMMA_I2C_QTRA,"CONN1,CONN2",Adafruit 0.56 7-Segment QT-import-fps:JST_SH4_RA,
